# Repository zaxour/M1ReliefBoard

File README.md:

# M1ReliefBoard
Small board to simplify soldering to Model 1 Genesis VDP RGB pins and reduce interference/jailbars.

Order the board in 1.6mm/0.062" thickness and it should fit cleanly under the RGB pins on the VDP. Use 30 AWG wire/enameled wire to connect, then use 28 AWG to go from the relief board to the 3BP.

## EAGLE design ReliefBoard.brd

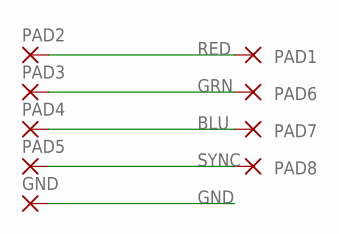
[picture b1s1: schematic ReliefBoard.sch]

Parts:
GND: SMD2; SMD1,27-2,54
PAD1, PAD2, PAD3, PAD4, PAD5, PAD6, PAD7, PAD8: SMD2; SMD1,27-2,54

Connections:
BLU: PAD4.1, PAD7.1
GND: GND.1
GRN: PAD3.1, PAD6.1
RED: PAD1.1, PAD2.1
SYNC: PAD5.1, PAD8.1

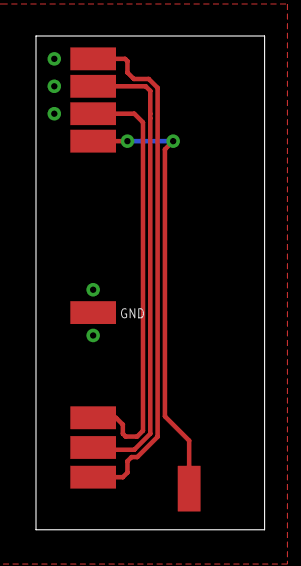
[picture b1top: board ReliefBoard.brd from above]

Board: 2 copper layers, 12.7 x 27.4 mm, 9 parts (0 on the bottom side), 4 nets.

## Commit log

2024-05-04 Add files via upload
    Add Most Recent Version and KiCad project
